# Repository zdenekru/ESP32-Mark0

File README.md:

# ESP32 Mark0

**ESP32 Mark0** is a powerful and not-so-compact IoT development project based on the ESP32-WROOM-32 microcontroller. This project showcases both hardware and firmware design, with a focus on wireless communication, embedded control, and a simple web dashboard interface.

---

## 🚀 Project Overview

ESP32 Mark0 is designed to:

- Prototype embedded systems using Wi-Fi and basic web interface
- Interface with sensors and other potential peripherals
- Provide a physical platform for experimenting with ESP32 capabilities
- Demonstrate firmware/web integration between Arduino and Python/HTML

> Developed step-by-step with the help of OpenAI's ChatGPT — from schematic to code.

---

## 🔧 Features

- **ESP32-WROOM-32** module
- USB-C interface with **CH340** USB-to-Serial bridge
- Reset and Boot buttons
- Status LED
- Breadboard-compatible pinout
- Custom KiCad PCB (Rev0 and Rev1)
- Firmware written in **Arduino IDE**
- Python and HTML files edited in **VS Code**
- Manufactured via [JLCPCB.com](https://jlcpcb.com)

---

## 🗂️ Repository Structure

```
ESP32-Mark0/
├── 25Zak001 ESP32 Mark0-backups/ # Backup versions and old files
├── CodeESP32/ESP32_Mark0_Github_ready/ # Arduino firmware
├── CodePython/ # Python scripts and dashboard HTML
├── Manufacturing Files Rev0/ # Rev0 Gerbers and fab files
├── Manufacturing Files Rev1/ # Final Rev1 files for production
├── .kicad_ # KiCad project files (Rev0 and Rev1)
├── .gitignore
├── .gitattributes
├── README.md
├── fp-info-cache
├── qrCode.kicad_sym
└── 25Zak001 ESP32 Mark0.step # 3D model of the board
```

---

## 🛠️ Development Environment

### Prerequisites

- **Arduino IDE** with ESP32 board support
- USB-C cable
- **CH340** USB driver
- **KiCad** (for editing hardware files)
- **VS Code** (for editing HTML/Python dashboard files)

---

## ⚙️ Uploading Firmware

Upload the sketch via Arduino IDE after selecting the correct board and port:

- **Board**: ESP32 Dev Module
- **Upload Speed**: 115200
- **Port**: (as assigned by your system)

---

## 🌐 Web Dashboard

The web dashboard (in `CodePython/`) includes a lightweight HTML interface that interacts with the ESP32 over Wi-Fi. Customize this dashboard for sensor readouts, toggles, or control logic.

---

## 🏭 Manufacturing

Both **Rev0** and **Rev1** were designed in **KiCad** and manufactured via **[JLCPCB](https://jlcpcb.com)**. All Gerber, BOM, and position files are provided in the respective manufacturing folders.

---

## 🤖 AI-Assisted Engineering

This project was co-developed with **ChatGPT**, assisting in:

- ESP32 firmware debugging and optimization
- PCB design decisions and validation
- HTML/Python dashboard integration
- Repository structure and documentation

---

## 📜 License

MIT License – see `LICENSE` file.

---

Made with ☕, perseverance, and ChatGPT.

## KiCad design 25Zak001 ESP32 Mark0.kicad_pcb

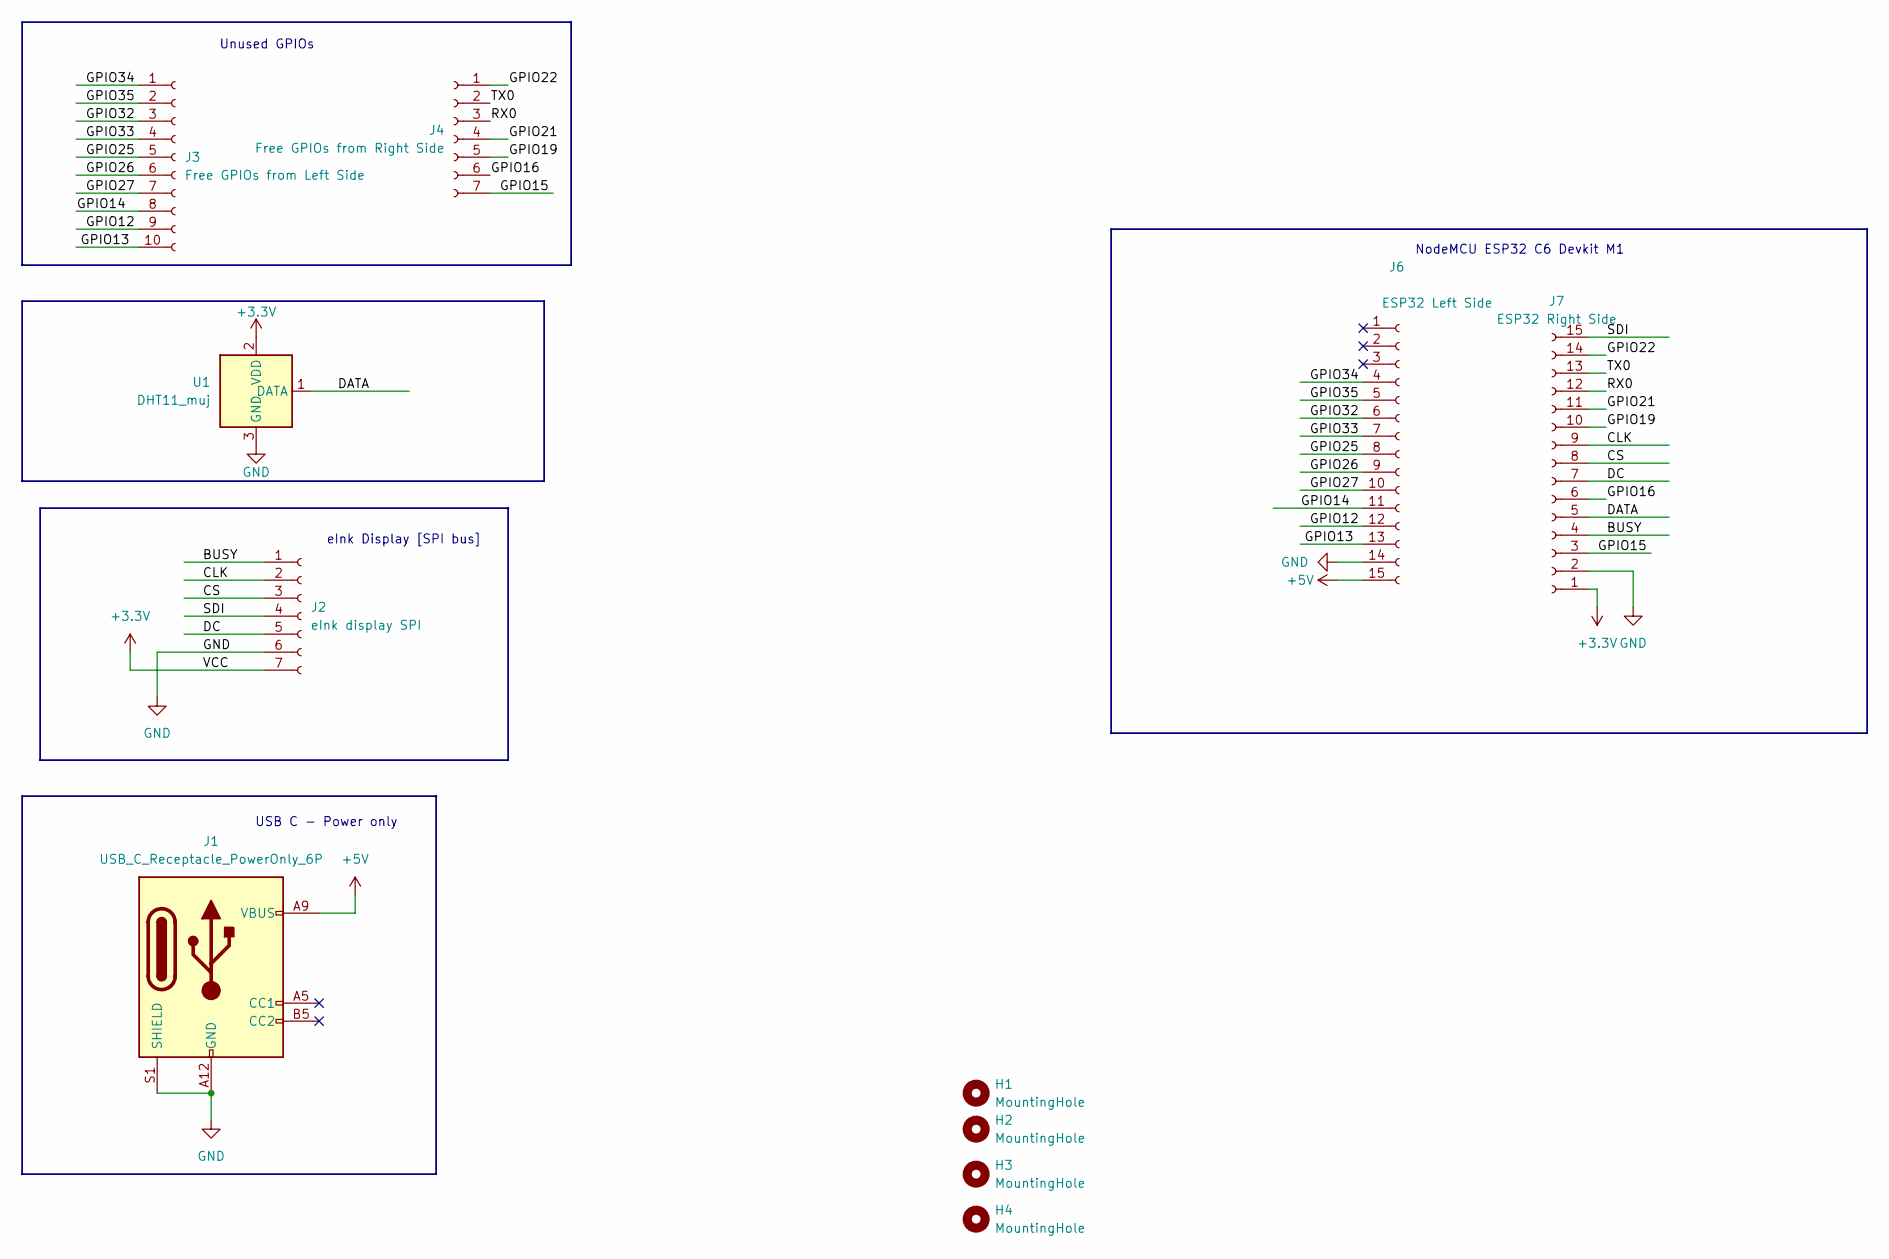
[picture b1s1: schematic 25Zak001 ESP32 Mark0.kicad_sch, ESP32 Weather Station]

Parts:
H1, H2, H3, H4: MountingHole; MountingHole_3.2mm_M3_ISO14580_Pad_TopBottom
J1: USB_C_Receptacle_PowerOnly_6P; USB_C_Receptacle_GCT_USB4135-GF-A_6P_TopMnt_Horizontal
J2: eInk display SPI; PinSocket_1x07_P2.54mm_Vertical
J3: Free GPIOs from Left Side; PinSocket_1x10_P2.54mm_Vertical
J4: Free GPIOs from Right Side; PinSocket_1x07_P2.54mm_Vertical
J6: ESP32 Left Side; PinSocket_1x15_P2.54mm_Vertical
J7: ESP32 Right Side; PinSocket_1x15_P2.54mm_Vertical
U1: DHT11_muj; PinSocket_1x03_P2.54mm_Vertical

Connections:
+3.3V: J2.7, J7.1, U1.2 (VDD)
+5V: J1.A9 (VBUS), J1.B9 (VBUS), J6.15
/BUSY: J2.1, J7.4
/CLK: J2.2, J7.9
/CS: J2.3, J7.8
/DATA: J7.5, U1.1 (DATA)
/DC: J2.5, J7.7
/GPIO12: J3.9, J6.12
/GPIO13: J3.10, J6.13
/GPIO14: J3.8, J6.11
/GPIO15: J4.7, J7.3
/GPIO16: J4.6, J7.6
/GPIO19: J4.5, J7.10
/GPIO21: J4.4, J7.11
/GPIO22: J4.1, J7.14
/GPIO25: J3.5, J6.8
/GPIO26: J3.6, J6.9
/GPIO27: J3.7, J6.10
/GPIO32: J3.3, J6.6
/GPIO33: J3.4, J6.7
/GPIO34: J3.1, J6.4
/GPIO35: J3.2, J6.5
/RX0: J4.3, J7.12
/SDI: J2.4, J7.15
/TX0: J4.2, J7.13
GND: J1.A12 (GND), J1.B12 (GND), J1.S1 (SHIELD), J2.6, J6.14, J7.2, U1.3 (GND)

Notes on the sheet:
USB C - Power only
eInk Display [SPI bus]
NodeMCU ESP32 C6 Devkit M1
Unused GPIOs

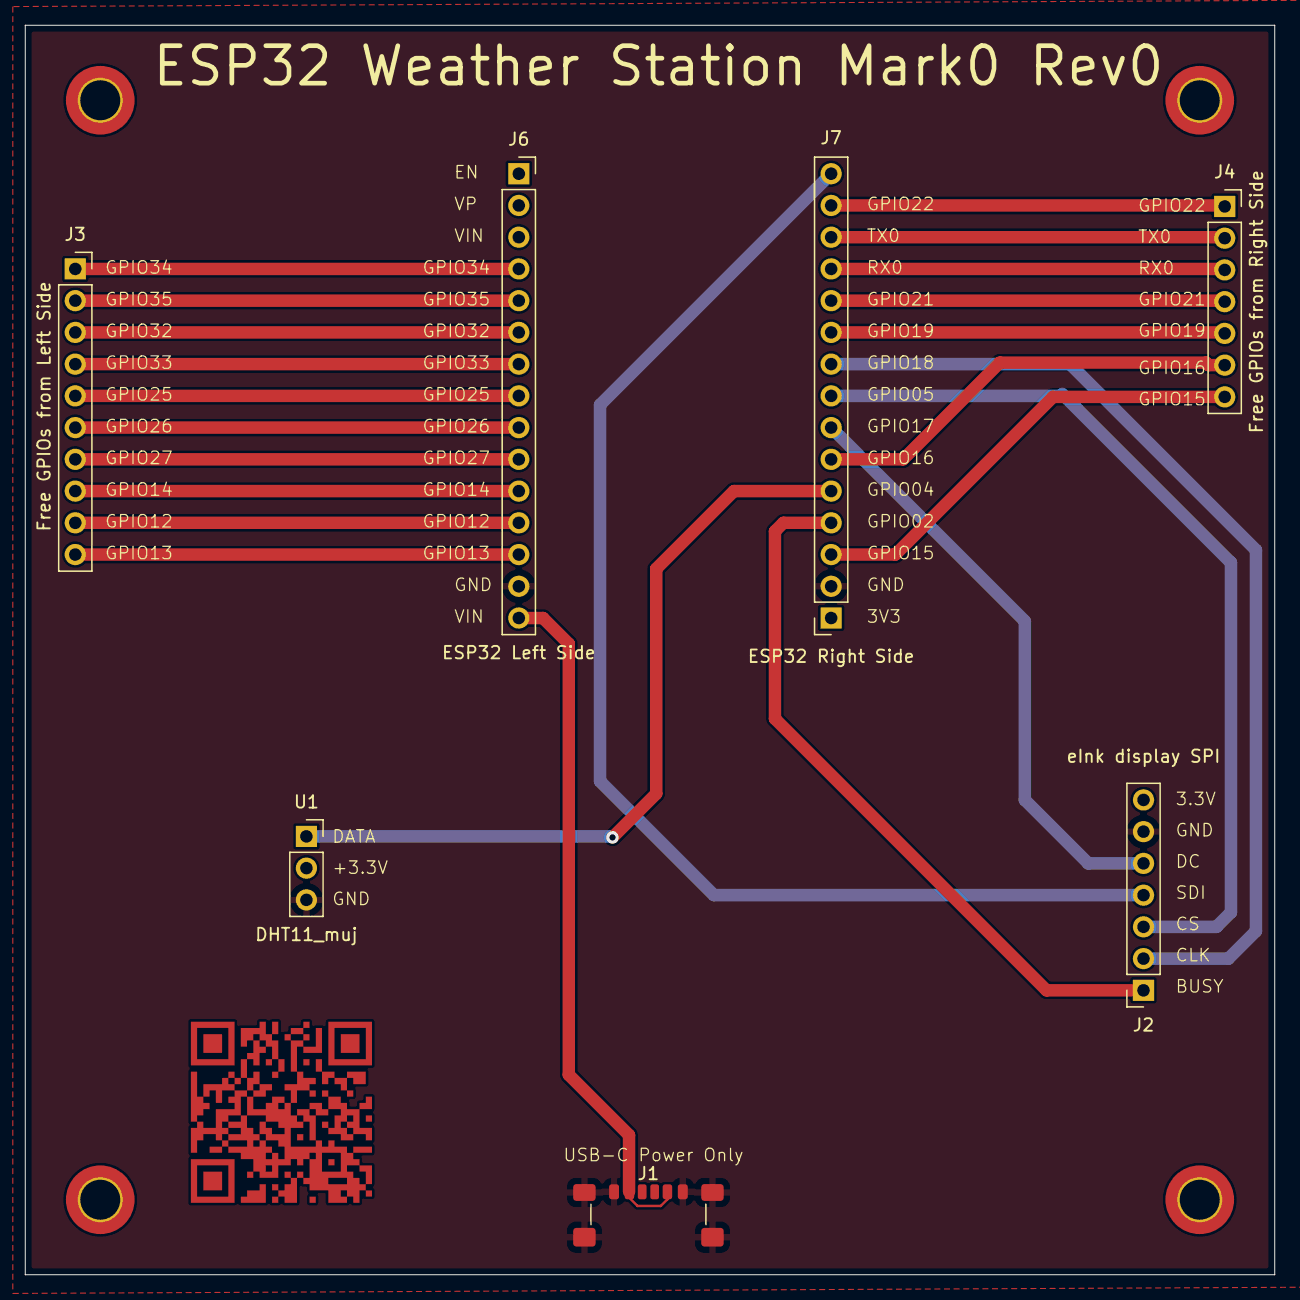
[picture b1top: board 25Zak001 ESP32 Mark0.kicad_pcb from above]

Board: 2 copper layers, 100.0 x 100.0 mm, 12 parts (0 on the bottom side), 26 nets.

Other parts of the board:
QR*****: QR_kod_esp32_mod0

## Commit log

2025-03-15 Prvni nahradni projektu
2025-03-15 Pridano USB C
2025-03-16 Nova verze
2025-03-16 Dokonceni, plno chyb, nutno opravit
2025-04-03 Added code
2025-05-10 Fairly Big Update
    - completly reworked ESP32 devkit
    - different sensor
    - all unused GPIOs are now available via sockets
2025-05-24 Rev1 created for PCB
    Because Rev0 is virutally unusable in current state.
2025-06-06 added functional code
2025-06-06 Fixed communication
    humidity is showing, temperature not, I have to work on that
2025-06-06 Update app.py
    temperature fixed
2025-06-06 Update dashboard.html
    Okay, everything works now, this is a milestone.
2025-06-06 updated README and LICENSE
2025-06-06 Fixing arduinoIDE file
